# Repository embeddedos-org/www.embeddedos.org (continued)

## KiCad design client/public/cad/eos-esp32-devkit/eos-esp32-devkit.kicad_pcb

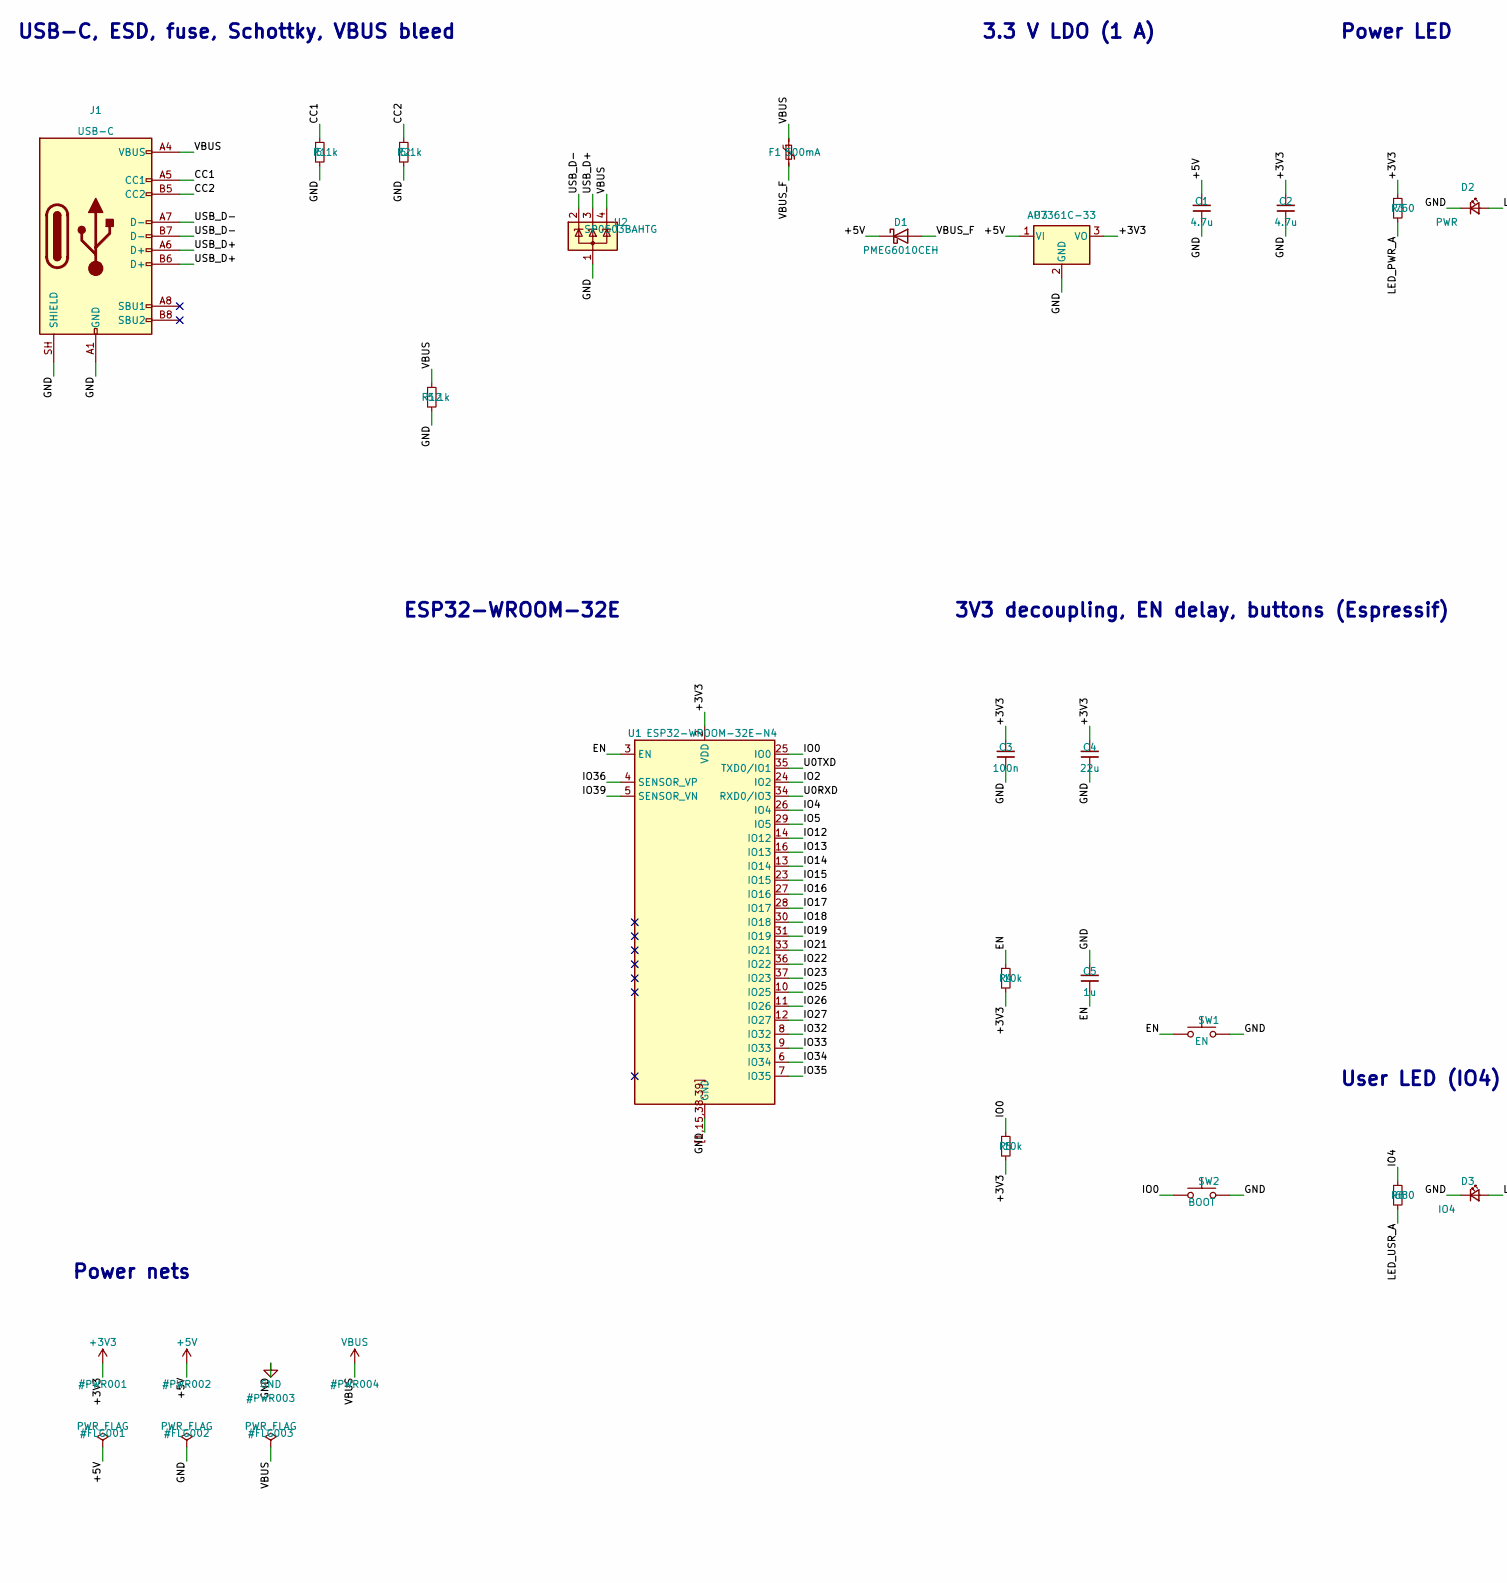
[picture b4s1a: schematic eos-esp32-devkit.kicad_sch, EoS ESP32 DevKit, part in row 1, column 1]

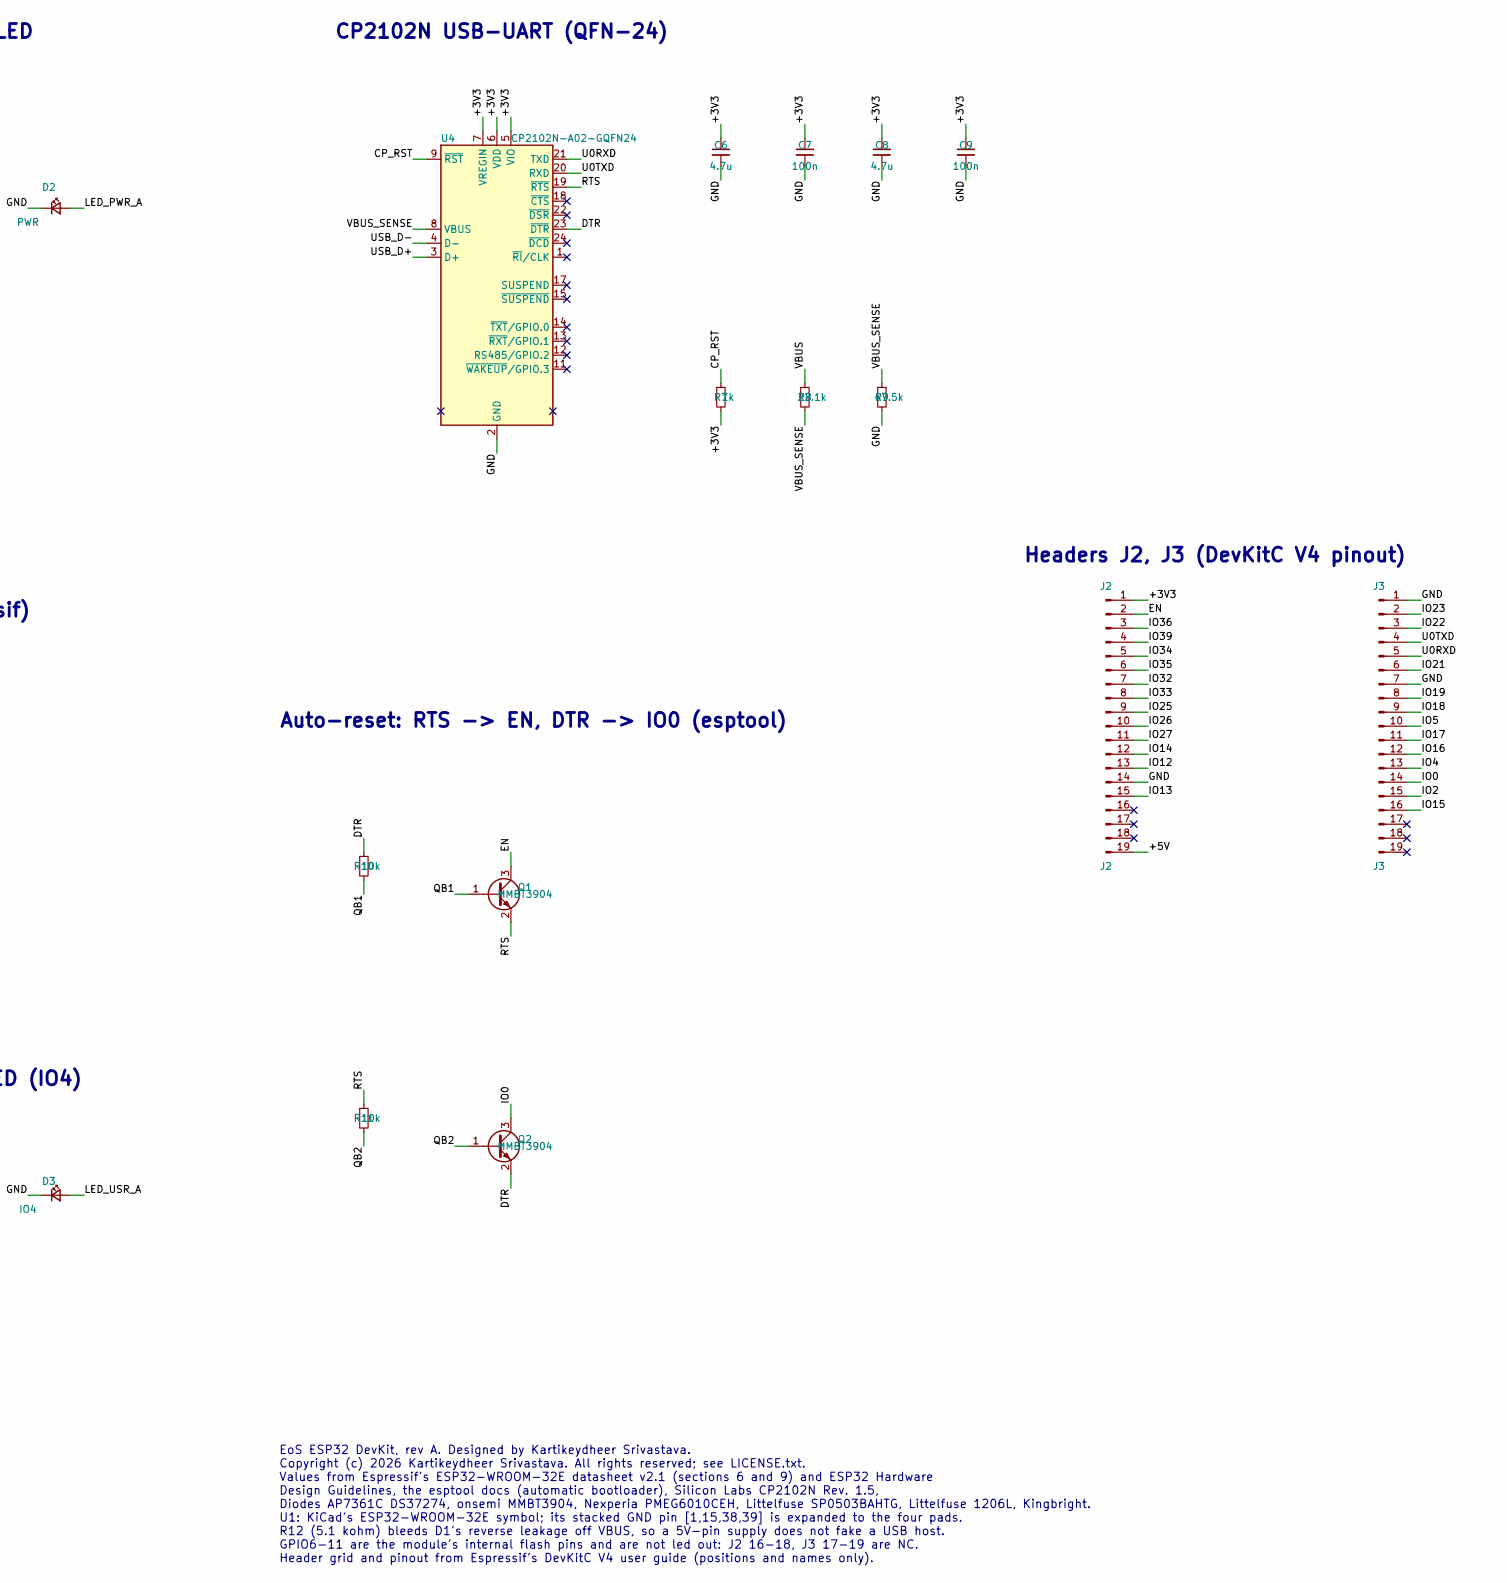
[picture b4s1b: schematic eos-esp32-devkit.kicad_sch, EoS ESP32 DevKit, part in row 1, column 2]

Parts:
C1, C2, C6, C8: 4.7u; C_0603_1608Metric
C3, C7, C9: 100n; C_0402_1005Metric
C4: 22u; C_0805_2012Metric
C5: 1u; C_0402_1005Metric
D1: PMEG6010CEH; D_SOD-123F; MPN PMEG6010CEH
D2: PWR; LED_0603_1608Metric; MPN APTD1608LSURCK
D3: IO4; LED_0603_1608Metric; MPN APTD1608LCGCK
F1: 500mA; Fuse_1206_3216Metric; MPN 1206L050YR
J1: USB-C; USB_C_Receptacle_HRO_TYPE-C-31-M-12; MPN TYPE-C-31-M-12
J2: J2; PinHeader_1x19_P2.54mm_Vertical
J3: J3; PinHeader_1x19_P2.54mm_Vertical
Q1, Q2: MMBT3904; SOT-23; MPN MMBT3904LT1G
R1, R2, R12: 5.1k; R_0402_1005Metric
R3: 750; R_0402_1005Metric
R4, R5, R10, R11: 10k; R_0402_1005Metric
R6: 680; R_0402_1005Metric
R7: 1k; R_0402_1005Metric
R8: 22.1k; R_0402_1005Metric
R9: 47.5k; R_0402_1005Metric
SW1: EN; SW_Push_1P1T_NO_CK_KMR2; MPN KMR221G LFS
SW2: BOOT; SW_Push_1P1T_NO_CK_KMR2; MPN KMR221G LFS
U1: ESP32-WROOM-32E-N4; ESP32-WROOM-32E; MPN ESP32-WROOM-32E-N4
U2: SP0503BAHTG; SOT-143; MPN SP0503BAHTG
U3: AP7361C-33; SOT-223-3_TabPin2; MPN AP7361C-33E-13
U4: CP2102N-A02-GQFN24; QFN-24-1EP_4x4mm_P0.5mm_EP2.6x2.6mm; MPN CP2102N-A02-GQFN24R

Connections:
+3V3: C2.1, C3.1, C4.1, C6.1, C7.1, C8.1, C9.1, J2.1, R3.1, R4.2, R5.2, R7.2, U1.2 (VDD), U3.3 (VO), U4.5 (VIO), U4.6 (VDD), U4.7 (VREGIN)
+5V: C1.1, D1.1 (K), J2.19, U3.1 (VI)
/CC1: J1.A5 (CC1), R1.1
/CC2: J1.B5 (CC2), R2.1
/CP_RST: R7.1, U4.9 (~RST)
/DTR: Q2.2 (E), R10.1, U4.23 (~DTR)
/EN: C5.2, J2.2, Q1.3 (C), R4.1, SW1.1, U1.3 (EN)
/IO0: J3.14, Q2.3 (C), R5.1, SW2.1, U1.25 (IO0)
/IO2: J3.15, U1.24 (IO2)
/IO4: J3.13, R6.1, U1.26 (IO4)
/IO5: J3.10, U1.29 (IO5)
/IO12: J2.13, U1.14 (IO12)
/IO13: J2.15, U1.16 (IO13)
/IO14: J2.12, U1.13 (IO14)
/IO15: J3.16, U1.23 (IO15)
/IO16: J3.12, U1.27 (IO16)
/IO17: J3.11, U1.28 (IO17)
/IO18: J3.9, U1.30 (IO18)
/IO19: J3.8, U1.31 (IO19)
/IO21: J3.6, U1.33 (IO21)
/IO22: J3.3, U1.36 (IO22)
/IO23: J3.2, U1.37 (IO23)
/IO25: J2.9, U1.10 (IO25)
/IO26: J2.10, U1.11 (IO26)
/IO27: J2.11, U1.12 (IO27)
/IO32: J2.7, U1.8 (IO32)
/IO33: J2.8, U1.9 (IO33)
/IO34: J2.5, U1.6 (IO34)
/IO35: J2.6, U1.7 (IO35)
/IO36: J2.3, U1.4 (SENSOR_VP)
/IO39: J2.4, U1.5 (SENSOR_VN)
/LED_PWR_A: D2.2 (A), R3.2
/LED_USR_A: D3.2 (A), R6.2
/QB1: Q1.1 (B), R10.2
/QB2: Q2.1 (B), R11.2
/RTS: Q1.2 (E), R11.1, U4.19 (~RTS)
/U0RXD: J3.5, U1.34 (RXD0/IO3), U4.21 (TXD)
/U0TXD: J3.4, U1.35 (TXD0/IO1), U4.20 (RXD)
/USB_D+: J1.A6 (D+), J1.B6 (D+), U2.3 (K), U4.3 (D+)
/USB_D-: J1.A7 (D-), J1.B7 (D-), U2.2 (K), U4.4 (D-)
/VBUS_F: D1.2 (A), F1.2
/VBUS_SENSE: R8.2, R9.1, U4.8 (VBUS)
GND: C1.2, C2.2, C3.2, C4.2, C5.1, C6.2, C7.2, C8.2, C9.2, D2.1 (K), D3.1 (K), J1.A1 (GND), J1.A12 (GND), J1.B1 (GND), J1.B12 (GND), J1.SH (SHIELD), J2.14, J3.1, J3.7, R1.2, R2.2, R9.2, R12.2, SW1.2, SW2.2, U1.1, U1.15, U1.38, U1.39, U1.[1,15,38,39] (GND), U2.1 (A), U3.2 (GND), U4.2 (GND), U4.25 (GND)
VBUS: F1.1, J1.A4 (VBUS), J1.A9 (VBUS), J1.B4 (VBUS), J1.B9 (VBUS), R8.1, R12.1, U2.4 (K)

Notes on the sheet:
USB-C, ESD, fuse, Schottky, VBUS bleed
3.3 V LDO (1 A)
Power LED
ESP32-WROOM-32E
3V3 decoupling, EN delay, buttons (Espressif)
User LED (IO4)
CP2102N USB-UART (QFN-24)
Auto-reset: RTS -> EN, DTR -> IO0 (esptool)
Headers J2, J3 (DevKitC V4 pinout)
Power nets
EoS ESP32 DevKit, rev A. Designed by Kartikeydheer Srivastava. Copyright (c) 2026 Kartikeydheer Srivastava. All rights reserved; see LICENSE.txt. Values from Espressif's ESP32-WROOM-32E datasheet v2.1 (sections 6 and 9) and ESP32 Hardware Design Guidelines, the esptool docs (automatic bootloader), 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

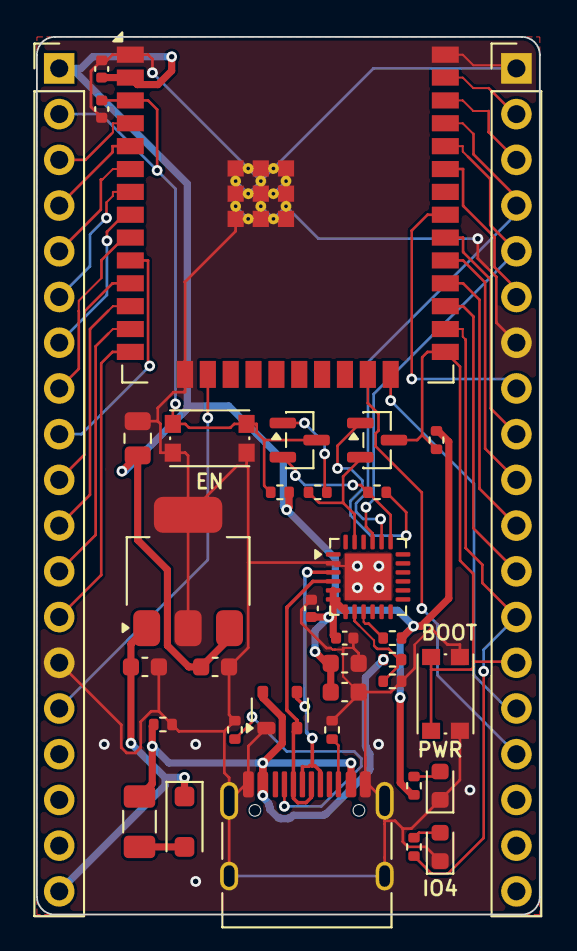
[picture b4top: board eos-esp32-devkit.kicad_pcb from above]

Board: 2 copper layers, 27.9 x 48.8 mm, 36 parts (0 on the bottom side), 44 nets.

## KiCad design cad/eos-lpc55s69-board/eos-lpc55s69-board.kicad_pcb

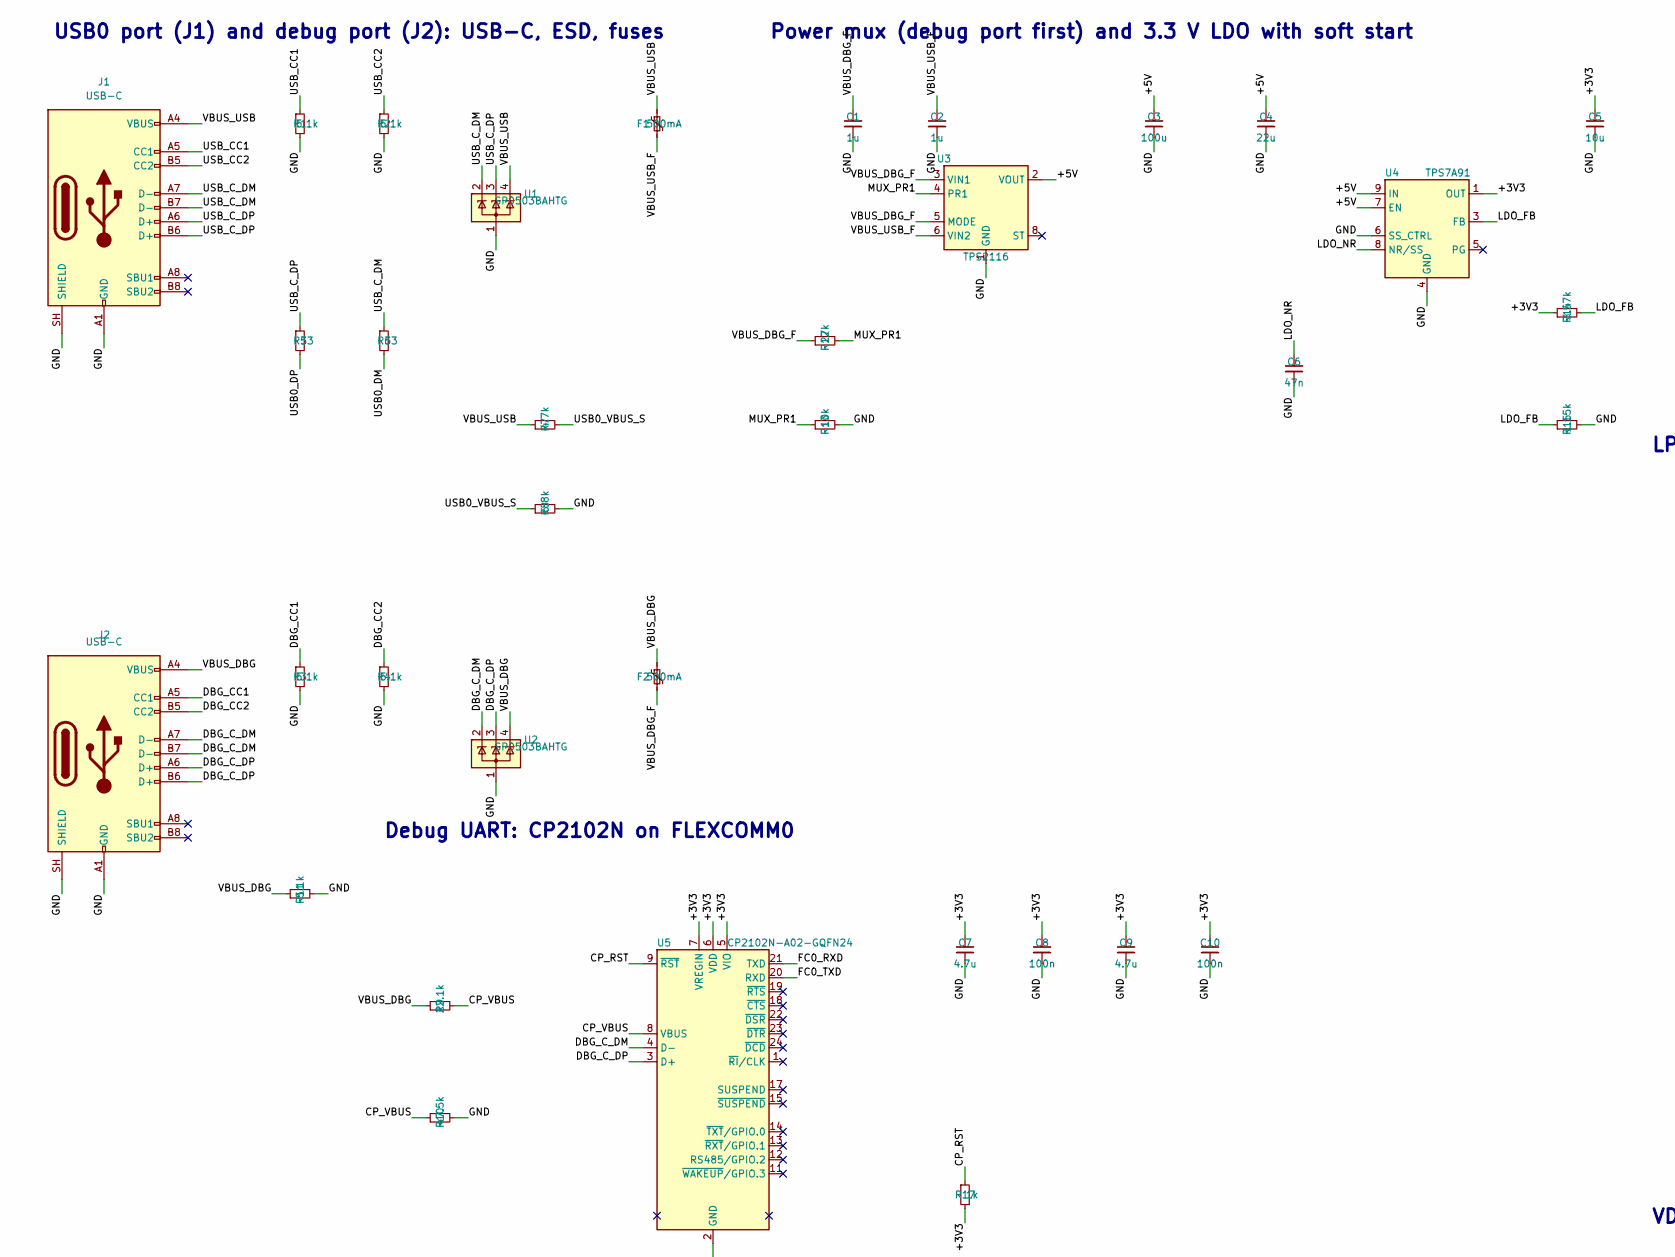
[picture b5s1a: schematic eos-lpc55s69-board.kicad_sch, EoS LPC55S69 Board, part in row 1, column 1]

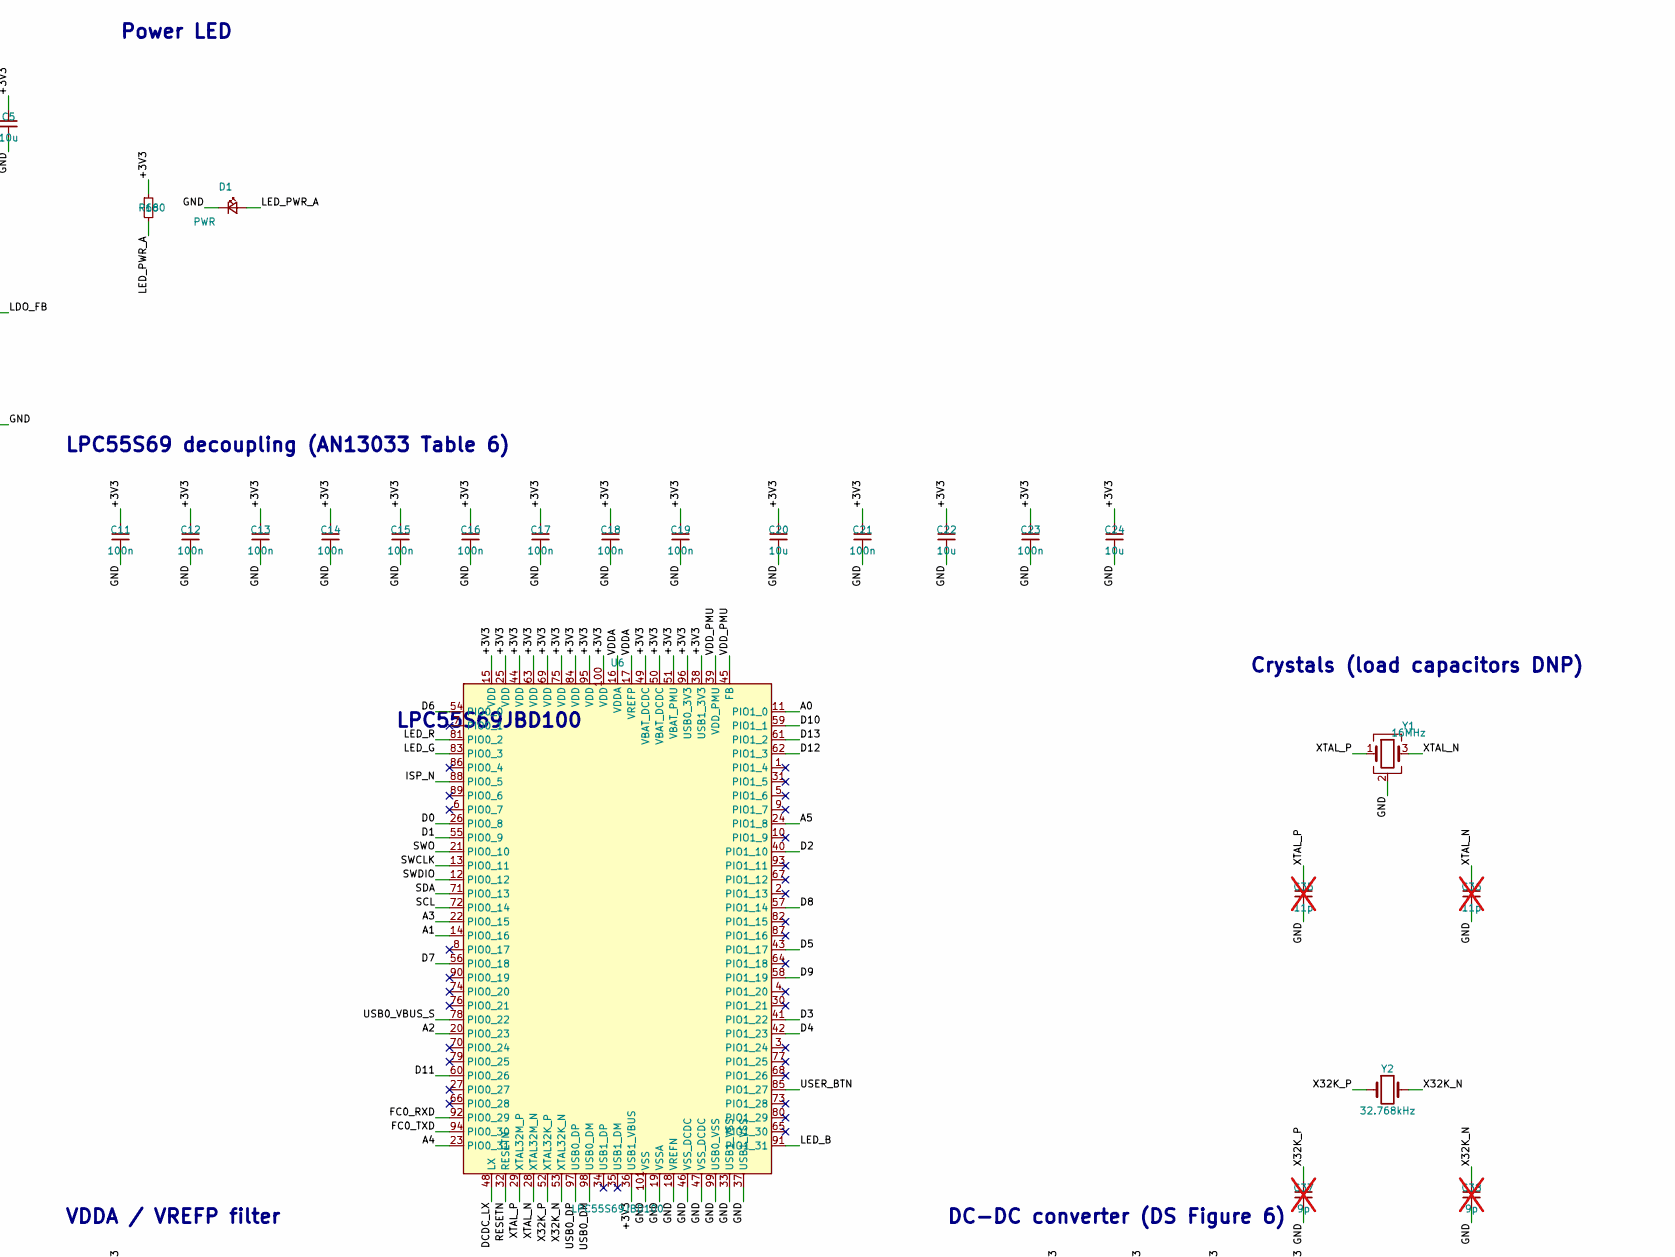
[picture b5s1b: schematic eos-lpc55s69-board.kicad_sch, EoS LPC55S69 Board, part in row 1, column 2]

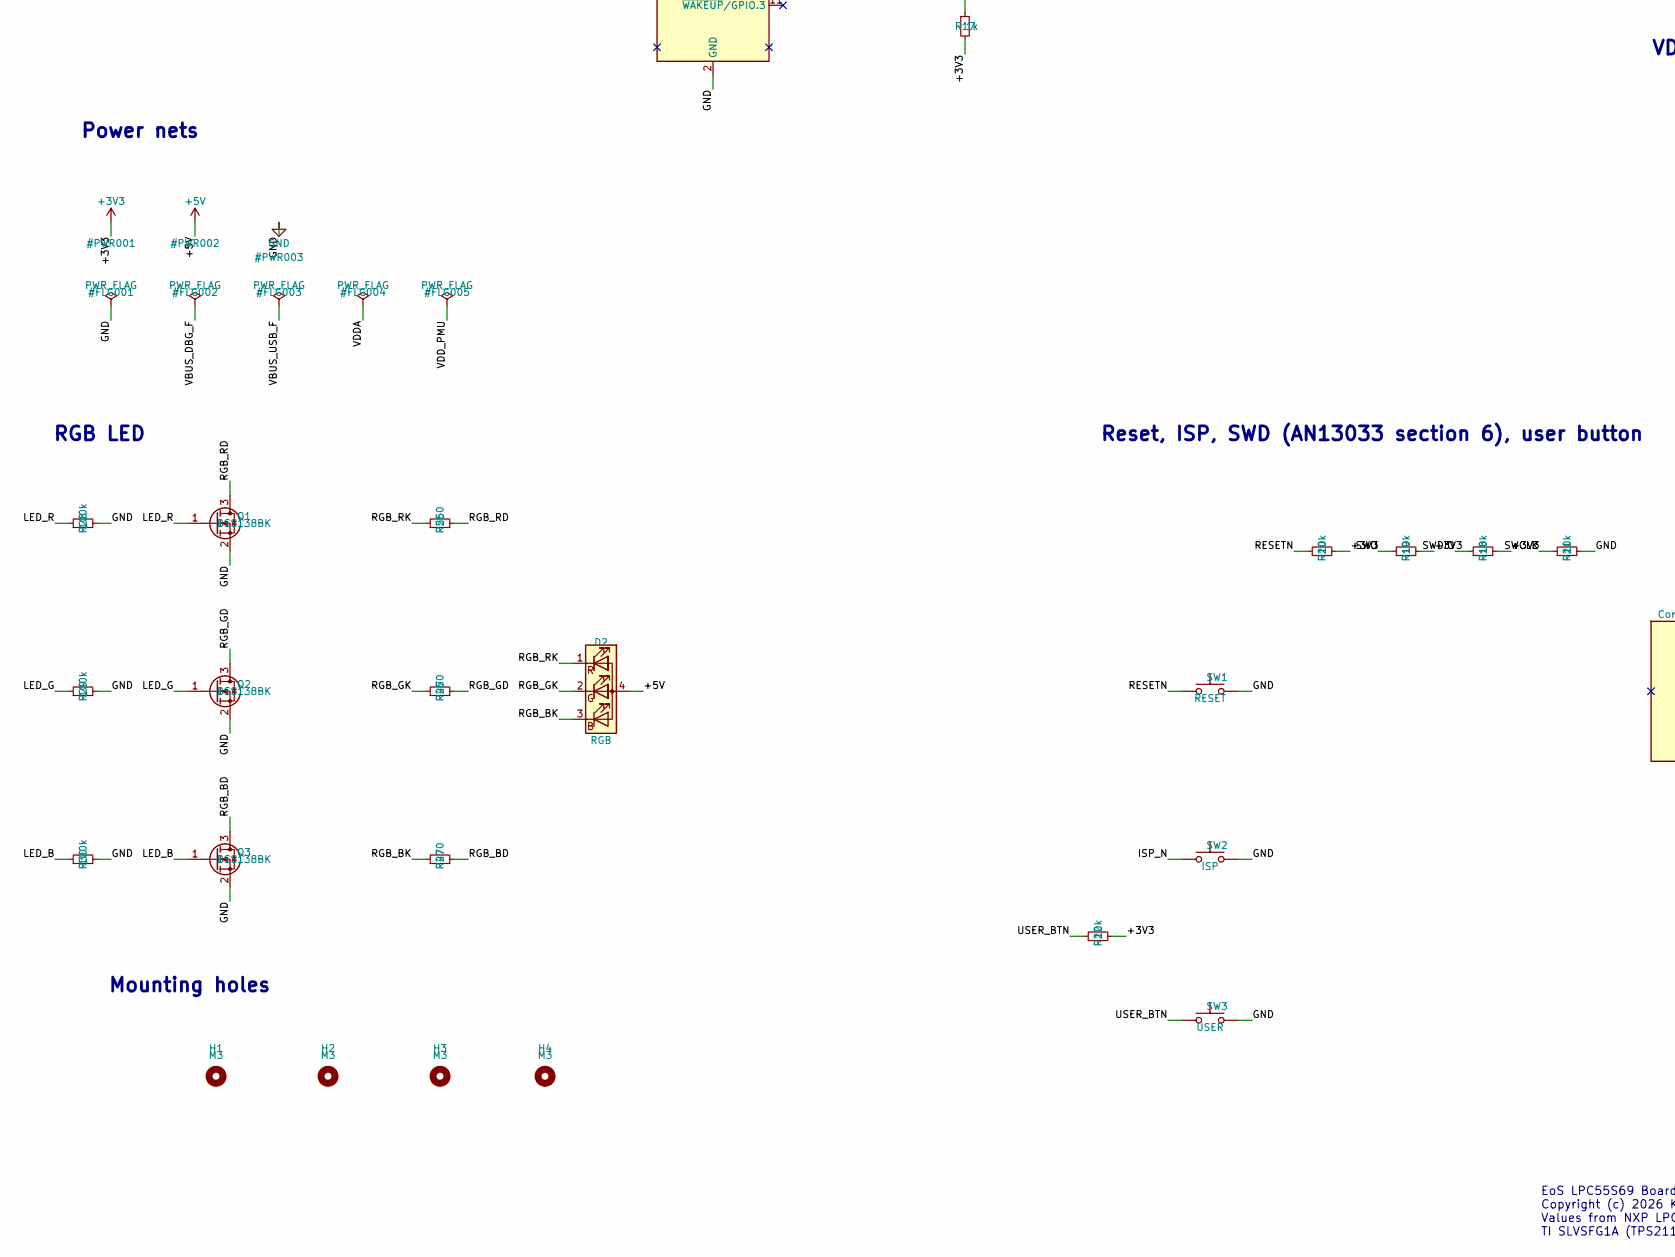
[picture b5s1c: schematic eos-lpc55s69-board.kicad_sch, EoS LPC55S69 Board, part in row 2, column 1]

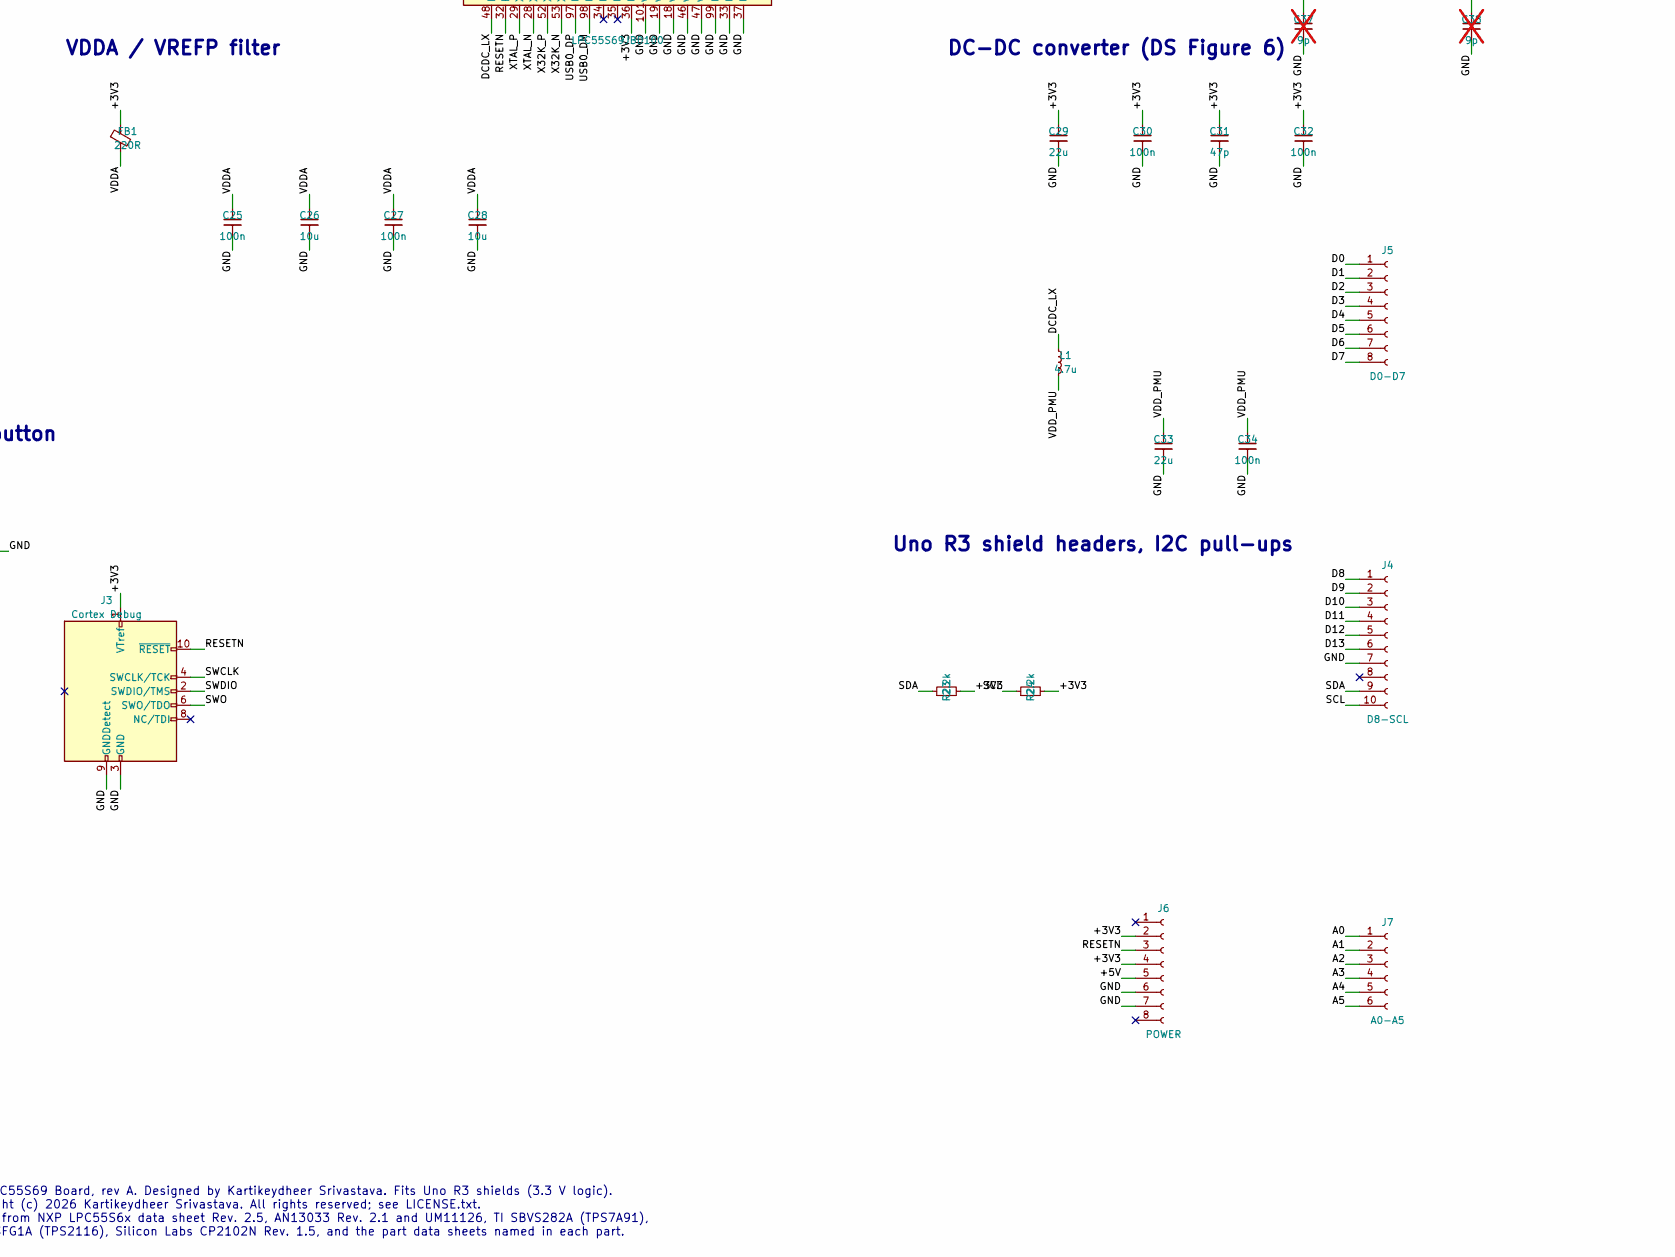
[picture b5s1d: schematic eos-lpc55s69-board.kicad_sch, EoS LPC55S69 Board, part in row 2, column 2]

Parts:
C1, C2: 1u; C_0402_1005Metric
C3: 100u; C_1210_3225Metric; MPN GRM32ER61A107ME20L
C4, C29, C33: 22u; C_0805_2012Metric; MPN GRM21BR61A226ME51L
C5: 10u; C_0805_2012Metric; MPN GRM21BR61C106KE15L
C6: 47n; C_0402_1005Metric; MPN GRM155R71C473KA01D
C7, C9: 4.7u; C_0603_1608Metric; MPN GRM188R61A475KE15D
C8, C10, C11, C12, C13, C14, C15, C16, C17, C18, C19, C21, C23, C25, C27, C30, C32, C34: 100n; C_0402_1005Metric; MPN CL05B104KO5NNNC
C20, C22, C24, C26, C28: 10u; C_0603_1608Metric; MPN GRM188R61A106MAALD
C31: 47p; C_0402_1005Metric; MPN GRM1555C1H470JA01D
C35, C36: 11p; C_0402_1005Metric; not fitted
C37, C38: 9p; C_0402_1005Metric; not fitted
D1: PWR; LED_0603_1608Metric; MPN APTD1608LCGCK
D2: RGB; LED_LiteOn_LTST-C19HE1WT; MPN LTST-C19HE1WT
F1, F2: 500mA; Fuse_1206_3216Metric; MPN 1206L050YR
FB1: 220R; L_0603_1608Metric; MPN MH1608-221Y
H1, H2, H3, H4: M3; MountingHole_3.2mm_M3_ISO14580
J1, J2: USB-C; USB_C_Receptacle_HRO_TYPE-C-31-M-12; MPN TYPE-C-31-M-12
J3: Cortex Debug; PinHeader_2x05_P1.27mm_Vertical_SMD; MPN FTSH-105-01-L-DV-K
J4: D8-SCL; PinSocket_1x10_P2.54mm_Vertical; MPN SSW-110-01-T-S
J5: D0-D7; PinSocket_1x08_P2.54mm_Vertical; MPN SSW-108-01-T-S
J6: POWER; PinSocket_1x08_P2.54mm_Vertical; MPN SSW-108-01-T-S
J7: A0-A5; PinSocket_1x06_P2.54mm_Vertical; MPN SSW-106-01-T-S
L1: 4.7u; L_Bourns-SRN4018; MPN SRN4018-4R7M
Q1, Q2, Q3: BSS138BK; SOT-23; MPN BSS138BK,215
R1, R2, R3, R4, R11: 5.1k; R_0402_1005Metric
R5, R6: 33; R_0402_1005Metric
R7: 4.7k; R_0402_1005Metric
R8: 6.8k; R_0402_1005Metric
R9: 22.1k; R_0402_1005Metric
R10: 47.5k; R_0402_1005Metric
R12: 27k; R_0402_1005Metric
R13, R18, R19, R20, R21, R22: 10k; R_0402_1005Metric
R14: 3.57k; R_0402_1005Metric
R15: 1.15k; R_0402_1005Metric
R16: 680; R_0402_1005Metric
R17: 1k; R_0402_1005Metric
R23, R24: 2.2k; R_0402_1005Metric
R25: 560; R_0402_1005Metric
R26, R27: 470; R_0402_1005Metric
R28, R29, R30: 100k; R_0402_1005Metric
SW1: RESET; SW_Push_1P1T_NO_CK_KMR2; MPN KMR221G LFS
SW2: ISP; SW_Push_1P1T_NO_CK_KMR2; MPN KMR221G LFS
SW3: USER; SW_Push_1P1T_NO_CK_KMR2; MPN KMR221G LFS
U1, U2: SP0503BAHTG; SOT-143; MPN SP0503BAHTG
U3: TPS2116; SOT-583-8; MPN TPS2116DRLR
U4: TPS7A91; Texas_S-PDSO-N10_EP1.2x2mm; MPN TPS7A9101DSKR
U5: CP2102N-A02-GQFN24; QFN-24-1EP_4x4mm_P0.5mm_EP2.6x2.6mm; MPN CP2102N-A02-GQFN24R
U6: LPC55S69JBD100; HLQFP-100-1EP_14x14mm_P0.5mm_EP3.21x3.21mm; MPN LPC55S69JBD100K
Y1: 16MHz; Crystal_SMD_3225-4Pin_3.2x2.5mm; MPN ECS-160-8-33Q-JES-TR
Y2: 32.768kHz; Crystal_SMD_3215-2Pin_3.2x1.5mm; MPN ABS07-32.768KHZ-7-T

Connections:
+3V3: C5.1, C7.1, C8.1, C9.1, C10.1, C11.1, C12.1, C13.1, C14.1, C15.1, C16.1, C17.1, C18.1, C19.1, C20.1, C21.1, C22.1, C23.1, C24.1, C29.1, C30.1, C31.1, C32.1, FB1.1, J3.1 (VTref), J6.2, J6.4, R14.1, R16.1, R17.2, R18.2, R19.2, R20.2, R22.2, R23.2, R24.2, U4.1 (OUT), U4.2 (OUT), U5.5 (VIO), U5.6 (VDD), U5.7 (VREGIN), U6.15 (VDD), U6.25 (VDD), U6.36 (USB1_VBUS), U6.38 (USB1_3V3), U6.44 (VDD), U6.49 (VBAT_DCDC), U6.50 (VBAT_DCDC), U6.51 (VBAT_PMU), U6.63 (VDD), U6.69 (VDD), U6.75 (VDD), U6.84 (VDD), U6.95 (VDD), U6.96 (USB0_3V3), U6.100 (VDD)
+5V: C3.1, C4.1, D2.4 (A), J6.5, U3.2 (VOUT), U3.7 (VOUT), U4.7 (EN), U4.9 (IN), U4.10 (IN)
/A0: J7.1, U6.11 (PIO1_0)
/A1: J7.2, U6.14 (PIO0_16)
/A2: J7.3, U6.20 (PIO0_23)
/A3: J7.4, U6.22 (PIO0_15)
/A4: J7.5, U6.23 (PIO0_31)
/A5: J7.6, U6.24 (PIO1_8)
/CP_RST: R17.1, U5.9 (~RST)
/CP_VBUS: R9.2, R10.1, U5.8 (VBUS)
/D0: J5.1, U6.26 (PIO0_8)
/D1: J5.2, U6.55 (PIO0_9)
/D2: J5.3, U6.40 (PIO1_10)
/D3: J5.4, U6.41 (PIO1_22)
/D4: J5.5, U6.42 (PIO1_23)
/D5: J5.6, U6.43 (PIO1_17)
/D6: J5.7, U6.54 (PIO0_0)
/D7: J5.8, U6.56 (PIO0_18)
/D8: J4.1, U6.57 (PIO1_14)
/D9: J4.2, U6.58 (PIO1_19)
/D10: J4.3, U6.59 (PIO1_1)
/D11: J4.4, U6.60 (PIO0_26)
/D12: J4.5, U6.62 (PIO1_3)
/D13: J4.6, U6.61 (PIO1_2)
/DBG_CC1: J2.A5 (CC1), R3.1
/DBG_CC2: J2.B5 (CC2), R4.1
/DBG_C_DM: J2.A7 (D-), J2.B7 (D-), U2.2 (K), U5.4 (D-)
/DBG_C_DP: J2.A6 (D+), J2.B6 (D+), U2.3 (K), U5.3 (D+)
/DCDC_LX: L1.1, U6.48 (LX)
/FC0_RXD: U5.21 (TXD), U6.92 (PIO0_29)
/FC0_TXD: U5.20 (RXD), U6.94 (PIO0_30)
/ISP_N: SW2.1, U6.88 (PIO0_5)
/LDO_FB: R14.2, R15.1, U4.3 (FB)
/LDO_NR: C6.1, U4.8 (NR/SS)
/LED_B: Q3.1 (G), R30.1, U6.91 (PIO1_31)
/LED_G: Q2.1 (G), R29.1, U6.83 (PIO0_3)
/LED_PWR_A: D1.2 (A), R16.2
/LED_R: Q1.1 (G), R28.1, U6.81 (PIO0_2)
/MUX_PR1: R12.2, R13.1, U3.4 (PR1)
/RESETN: J3.10 (~RESET), J6.3, R20.1, SW1.1, U6.32 (RESETN)
/RGB_BD: Q3.3 (D), R27.2
/RGB_BK: D2.3 (BK), R27.1
/RGB_GD: Q2.3 (D), R26.2
/RGB_GK: D2.2 (GK), R26.1
/RGB_RD: Q1.3 (D), R25.2
/RGB_RK: D2.1 (RK), R25.1
/SCL: J4.10, R24.1, U6.72 (PIO0_14)
/SDA: J4.9, R23.1, U6.71 (PIO0_13)
/SWCLK: J3.4 (SWCLK/TCK), R21.1, U6.13 (PIO0_11)
/SWDIO: J3.2 (SWDIO/TMS), R18.1, U6.12 (PIO0_12)
/SWO: J3.6 (SWO/TDO), R19.1, U6.21 (PIO0_10)
/USB0_DM: R6.2, U6.98 (USB0_DM)
/USB0_DP: R5.2, U6.97 (USB0_DP)
/USB0_VBUS_S: R7.2, R8.1, U6.78 (PIO0_22)
/USB_CC1: J1.A5 (CC1), R1.1
/USB_CC2: J1.B5 (CC2), R2.1
/USB_C_DM: J1.A7 (D-), J1.B7 (D-), R6.1, U1.2 (K)
/USB_C_DP: J1.A6 (D+), J1.B6 (D+), R5.1, U1.3 (K)
/USER_BTN: R22.1, SW3.1, U6.85 (PIO1_27)
/VBUS_DBG: F2.1, J2.A4 (VBUS), J2.A9 (VBUS), J2.B4 (VBUS), J2.B9 (VBUS), R9.1, R11.1, U2.4 (K)
/VBUS_DBG_F: C1.1, F2.2, R12.1, U3.3 (VIN1), U3.5 (MODE)
/VBUS_USB: F1.1, J1.A4 (VBUS), J1.A9 (VBUS), J1.B4 (VBUS), J1.B9 (VBUS), R7.1, U1.4 (K)
/VBUS_USB_F: C2.1, F1.2, U3.6 (VIN2)
/VDDA: C25.1, C26.1, C27.1, C28.1, FB1.2, U6.16 (VDDA), U6.17 (VREFP)
/VDD_PMU: C33.1, C34.1, L1.2, U6.39 (VDD_PMU), U6.45 (FB)
/X32K_N: C38.1, U6.53 (XTAL32K_N), Y2.2
/X32K_P: C37.1, U6.52 (XTAL32K_P), Y2.1
/XTAL_N: C36.1, U6.28 (XTAL32M_N), Y1.3
/XTAL_P: C35.1, U6.29 (XTAL32M_P), Y1.1
GND: C1.2, C2.2, C3.2, C4.2, C5.2, C6.2, C7.2, C8.2, C9.2, C10.2, C11.2, C12.2, C13.2, C14.2, C15.2, C16.2, C17.2, C18.2, C19.2, C20.2, C21.2, C22.2, C23.2, C24.2, C25.2, C26.2, C27.2, C28.2, C29.2, C30.2, C31.2, C32.2, C33.2, C34.2, C35.2, C36.2, C37.2, C38.2, D1.1 (K), J1.A1 (GND), J1.A12 (GND), J1.B1 (GND), J1.B12 (GND), J1.SH (SHIELD), J2.A1 (GND), J2.A12 (GND), J2.B1 (GND), J2.B12 (GND), J2.SH (SHIELD), J3.3 (GND), J3.5 (GND), J3.9 (GNDDetect), J4.7, J6.6, J6.7, Q1.2 (S), Q2.2 (S), Q3.2 (S), R1.2, R2.2, R3.2, R4.2, R8.2, R10.2, R11.2, R13.2, R15.2, R21.2, R28.2, R29.2, R30.2, SW1.2, SW2.2, SW3.2, U1.1 (A), U2.1 (A), U3.1 (GND), U4.4 (GND), U4.6 (SS_CTRL), U4.11 (GND), U5.2 (GND), U5.25 (GND), U6.18 (VREFN), U6.19 (VSSA), U6.33 (USB1_VSS), U6.37 (USB1_VSS), U6.46 (VSS_DCDC), U6.47 (VSS_DCDC), U6.99 (USB0_VSS), U6.101 (VSS), Y1.2 (G), Y1.4 (G)

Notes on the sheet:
USB0 port (J1) and debug port (J2): USB-C, ESD, fuses
Power mux (debug port first) and 3.3 V LDO with soft start
Power LED
Debug UART: CP2102N on FLEXCOMM0
LPC55S69 decoupling (AN13033 Table 6)
LPC55S69JBD100
DC-DC converter (DS Figure 6)
Crystals (load capacitors DNP)
VDDA / VREFP filter
Reset, ISP, SWD (AN13033 section 6), user button
RGB LED
Uno R3 shield headers, I2C pull-ups
Mounting holes
Power nets
EoS LPC55S69 Board, rev A. Designed by Kartikeydheer Srivastava. Fits Uno R3 shields (3.3 V logic). Copyright (c) 2026 Kartikeydheer Srivastava. All rights reserved; see LICENSE.txt. Values from NXP LPC55S6x data sheet Rev. 2.5, AN13033 Rev. 2.1 and UM11126, TI SBVS282A (TPS7A91), TI SLVSFG1A (TPS2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

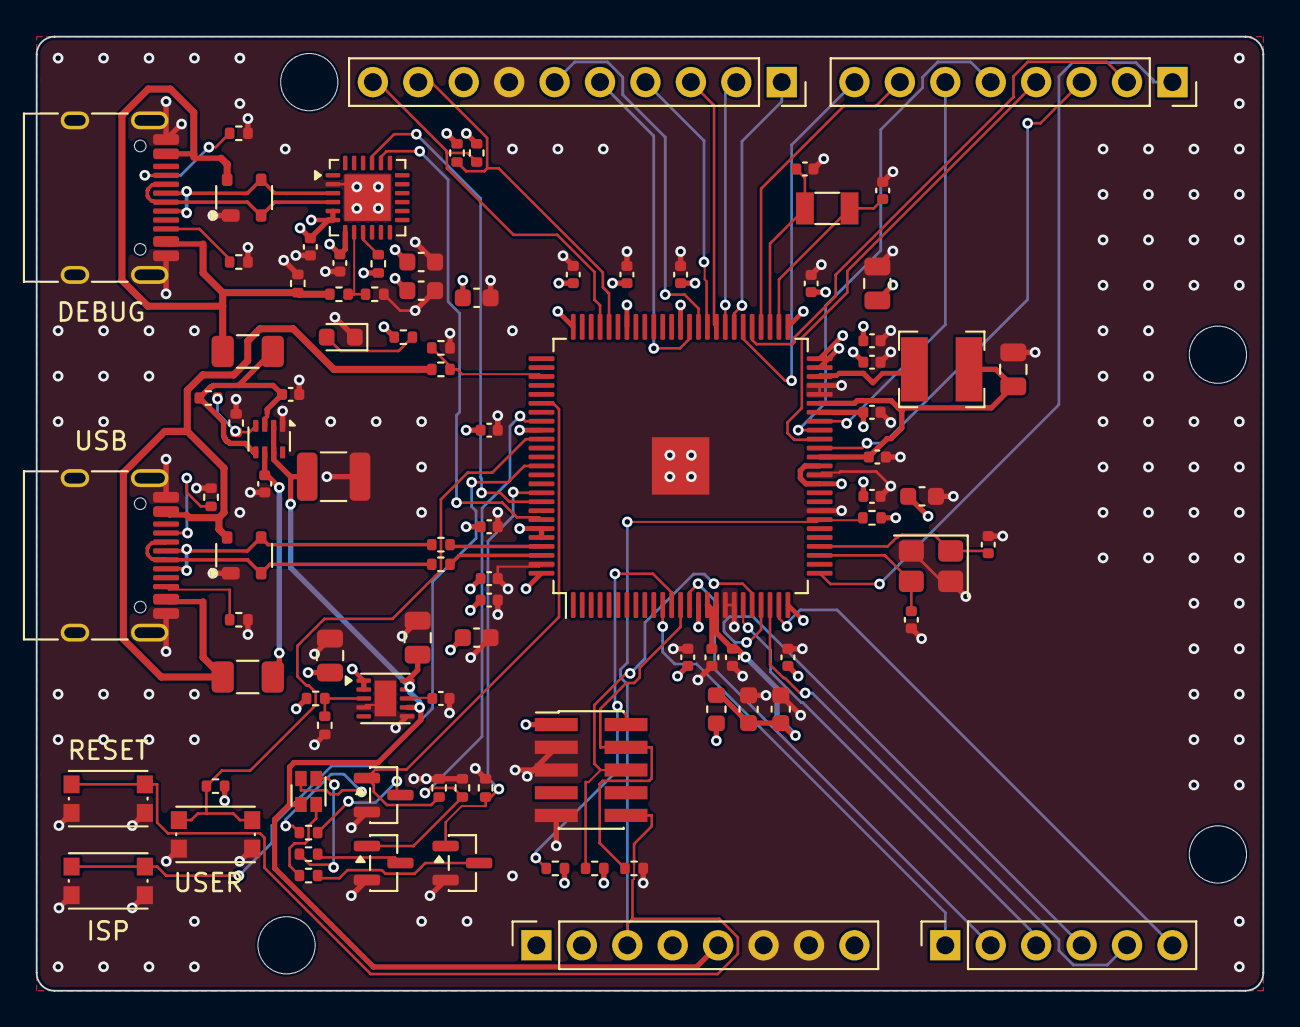
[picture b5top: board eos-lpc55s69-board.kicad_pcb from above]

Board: 4 copper layers, 68.6 x 53.3 mm, 99 parts (1 on the bottom side), 70 nets.
